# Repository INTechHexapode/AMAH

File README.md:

# AMAH : Automatic Markov-chain Actuated Hexapod
A hexapod robot that learns to walk by trial and errors, using Markov chain.

Please remark that I didn't design or build the robot itself (that was done by [Vincent Studer](https://fr.linkedin.com/in/vincent-studer-8179a864)).
My job was to program the leg control and the learning.

A few videos :
* [AMAH learns to stay upright](https://www.youtube.com/watch?v=HAIdLsz8gmg&feature=player_embedded)
* [Its first, painful walk](https://www.youtube.com/watch?v=2Z7JvmVVERA)
* [A presentation video, in french](https://www.youtube.com/watch?v=ZjIlJP-vDPI)
* [The dance of AMAH](https://www.facebook.com/190110074395003/videos/675518149187524/)

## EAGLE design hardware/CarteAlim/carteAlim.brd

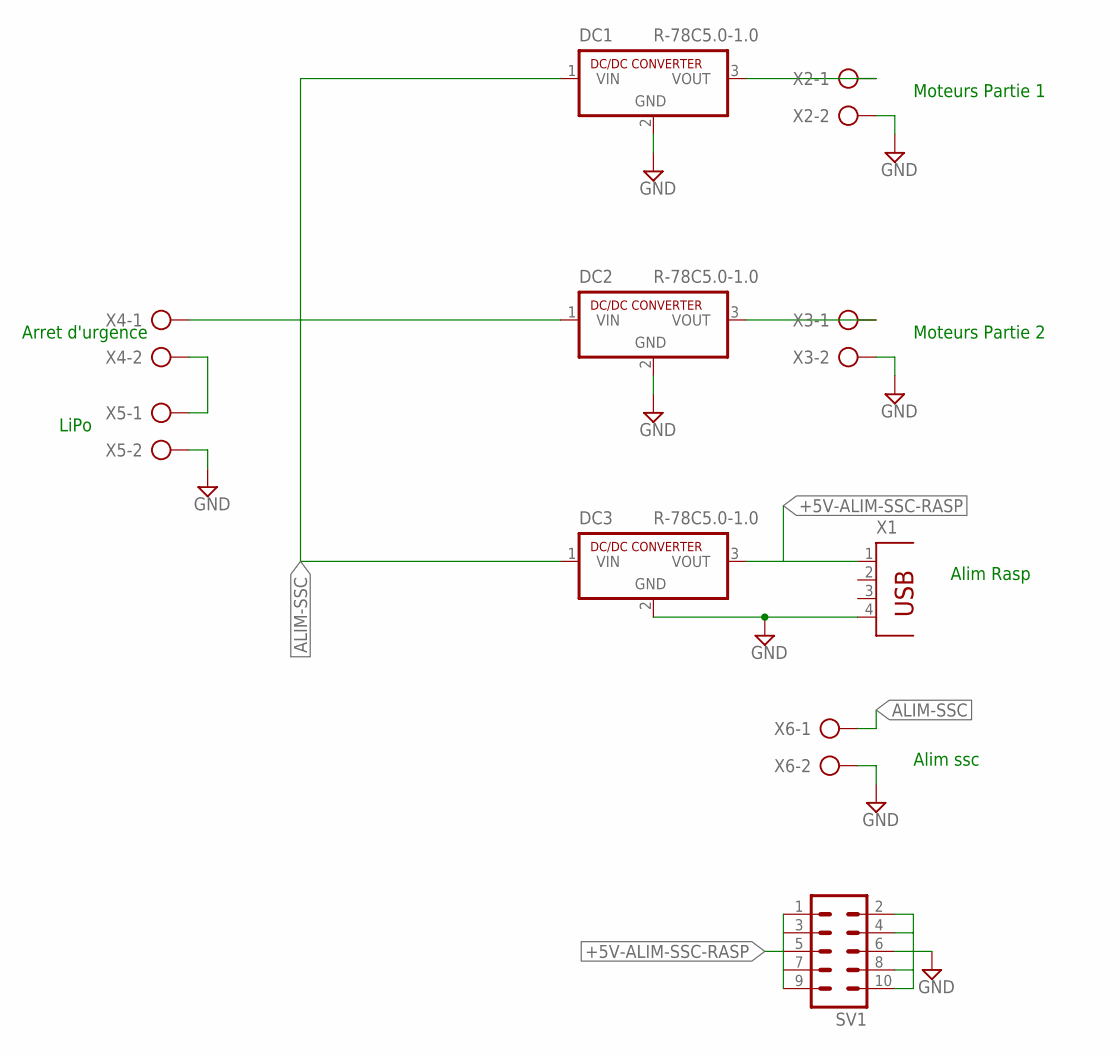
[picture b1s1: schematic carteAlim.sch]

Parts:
DC1, DC2, DC3: R-78C5.0-1.0; SIP3
SV1: MA05-2
X1: PN87520
X2, X3, X4, X5, X6: AK300/2

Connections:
+5V-ALIM-SSC-RASP: DC3.3 (VOUT), SV1.1, SV1.9, X1.1
ALIM-SSC: DC1.1 (VIN), DC2.1 (VIN), DC3.1 (VIN), X4.1, X6.1
GND: DC1.2 (GND), DC2.2 (GND), DC3.2 (GND), SV1.2, SV1.4, SV1.6, SV1.8, SV1.10, X1.4, X2.2, X3.2, X5.2, X6.2
unnamed: X4.2, X5.1
unnamed: DC1.3 (VOUT), X2.1
unnamed: DC2.3 (VOUT), X3.1

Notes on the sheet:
LiPo
Arret d'urgence
Moteurs Partie 1
Moteurs Partie 2
Alim Rasp
Alim ssc

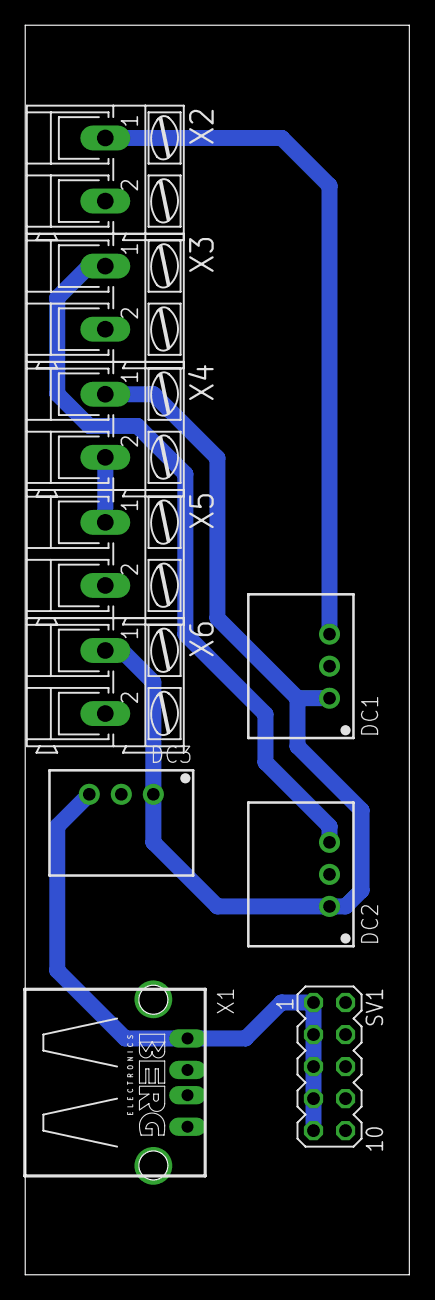
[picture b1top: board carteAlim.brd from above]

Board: 2 copper layers, 30.5 x 99.1 mm, 10 parts (0 on the bottom side), 6 nets.

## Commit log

2013-09-04 Mise en place de la structure du git
2013-09-04 Mise en place de la structure du git 2.0
2013-09-04 Ajout du script python
2013-09-06 Ajout de la classe serial
2013-09-06 Ajout des classes Hexapode, Servo et Leg
2013-09-06 Ajout de la compilatio nen C++11
2013-09-06 Test dans le main
2013-09-06 premiers tests, problème d'indexation des pattes dans Hexapod
2013-09-06 gitignore + modification de droits
2013-09-12 Ajout réseau de neuronne
2013-09-12 script python
2013-09-25 Ajout des 6 positions de pattes
2013-09-26 En mieux avec des enums
2014-02-10 Création du projet java
2014-02-10 Création des classes etat, hexapode, patte et moteur. Récupération du serialmanager d'intech.
2014-02-10 Complétion
2014-02-10 Une classe Markov aussi qui contiendra la chaîne
2014-02-11 EtatMoteur, EtatPatte, EtatHexa
2014-02-11 Oubli de commentaire
2014-02-12 Quelques TODO en plus
2014-02-17 Markov sérialisable
2014-02-17 Génération d'états aléatoires
2014-02-17 Quelques détails corrigés
2014-03-11 Ajout des classes pour gérer les enchaînements de tests
2014-03-11 Hexapode utilisé par le Test directement
2014-03-12 Rangement des classes de test dans un package à part
2014-03-15 Ping corrigé, lib en chemin relatif, protocole SSC-32
2014-03-16 Desasservissement, lever patte, baisser patte
2014-03-16 sauvegarde et chargement markov dans test, init() et terminate()
2014-03-16 Ajout init() et terminate() dans testEngine
2014-03-16 Lib série pour hexapode
2014-03-16 Encore serial
2014-03-16 Méthode change_moteur
2014-03-16 goto_etat de hexapode public
2014-03-16 Ajout de la méthode pour la maj matric
2014-03-16 Remplissage des fonctions de StandStill
2014-03-16 Getter et setter etat actuel sur hexapode
2014-03-16 Complétion de lever et baisser patte
2014-03-16 Correction du temps de pause et ajout de onBreak()
2014-03-16 Patte et EtatPatte
2014-03-16 init() dans le constructeur du testEngine
2014-03-16 On est presque prêt pour les tests
2014-03-16 Suppression de warnings
2014-03-17 Test réalisable, sérialisation à debugger
2014-03-17 .gitignore pour les sauvegardes de matrices
2014-03-17 Des commentaires
2014-03-18 classpath et project dans le gitignore
2014-03-18 Tuto à partir de zéro pour apprendre à installer la librxtx!!
2014-03-18 Premières sauvegardes de matrice
2014-03-18 Sauvegarde complète (avec logs/ aussi) ou partielle (sans logs/)
2014-03-18 ValidTest, sérialisation, accélération de l'apprentissage (on ne remonte que si on en a besoin)
2014-03-19 Debut de code pour l'affichage (n'est pas encore intégré)
2014-03-19 4 états pattes, debug test, log
2014-03-19 Markov avec 4 états
2014-03-19 série > /dev/null
2014-03-19 Surcharge next() avec la matrice pour tenir debout
2014-03-19 calculs à debugger
2014-03-24 Toujours pas possible de se servir de l'interface graphique, mais ça avance un minimum
2014-03-26 Ajout de la classe DataSaver qui encapsule des fonctions de sauvegarde et chargement des données.
2014-03-27 Sauvegarde de chaque étape du test pour pouvoir le rejouer plus tard. Non testé loul
2014-04-24 Et un gros commit qui tache avec trop de choses pour que je me souvienne de tout :
    - Grosse modif de markov pour avoir une matrice à deux dimension
    (standstilltest ne fonctionnera plus)
    - Début du test de coordination des pattes
2014-04-24 Ajout de la classe SocketClient, permettant de communiquer avec l'appli Android
2014-04-25 Conversion coordonnées (x,y) -> angles
2014-04-25 DataSaver avec suppression de fichiers
2014-04-25 Symétrie circulaire
2014-04-25 EtatPatte avec les nouveaux états
2014-04-25 Hexapode fait l'action contenue dans un String
2014-04-25 Debug patte et Markov
2014-04-25 Ajout du test d'apprentissage pour la coordination des pattes
2014-04-25 Rename des data
2014-04-25 EtatPatte peut aller à toutes les positions... mais faut encore debugger
2014-04-25 Ajout de l'override de toString
2014-04-25 Modification de next() pour renvoyer une position d'équilibre
2014-04-25 Ajout de l'etat_actuel comme attribut de Test. Rajout du nouveau test pour la coordination des pattes.
2014-04-25 Ménage de printemps, simplification, exception
2014-04-26 Ajout du test de simulation MAJ des données markov_equilibre Divers debugs, test de simulation toujours à debug.
2014-04-26 Suite du debug. TODO : Fix le save_test (classenon serializable) Check le getNum et la taille de la matrice
2014-04-26 Correction formule
2014-04-26 Test
2014-04-26 Ça marche super, rotation y compris
2014-04-26 MAJ EtatPatte => String
2014-04-26 Moteurs groupés
2014-04-26 Simulation fonctionne, rework EtatPatte=>String terminé
2014-04-26 Il en manquait un, loul
2014-04-26 simulation qui marche, valeurs à valider
2014-04-26 validation de test simulation
2014-04-26 Chargement matrice validation
2014-04-26 Gestion du temps
2014-04-26 Lanceur avec plusieurs méthodes disponibles
2014-04-26 Debug markov
2014-04-26 Méthodes haut niveau pour hexapode (avancer, va_au_point)
2014-04-26 goto_etat ne renvoie plus d'exception mais les traite lui-même
2014-04-26 Nouvelle marche à tester
2014-04-26 Méthode recaler, poser_fresque, symétrie rouge/jaune
2014-04-26 TODO list
2014-04-26 Correction angles min et max
2014-04-26 Quelques petites optimisations de code
2014-04-26 Vec2, suit_chemin
2014-04-26 Trajectoire horaire ou anti-horaire
2014-04-27 recaler réécrite
2014-04-27 De plus grandes enjambées
2014-04-27 Fin du match
2014-04-27 Utilisation du capteur
2014-04-27 Contournement de l'ennemi
2014-04-27 Gestion des bordures du terrain
2014-04-27 Ecart à la bordure
2014-04-27 Petit oubli
2014-04-27 Distance de détection
2014-04-27 Marche en ignorant certaines pattes
2014-04-27 Réorganisation du fichier Hexapode: les méthodes haut niveau sont en haut, les bas niveau en bas
2014-04-27 Debug + constantes
2014-04-27 Debug
2014-04-27 Debug au_au_point
2014-04-27 Pareil, mais sans les print
2014-04-27 Profils de marche (enjamber, aller loin, ...)
2014-04-27 J'ai essayé un mouvement triphasé, mais ça ne marche pas...
2014-04-27 Le lanceur aussi
2014-04-27 Baudrate à 38400
2014-04-27 On ne doit normalement pas spécifier de temps pour un moteur désasservi (cf datasheet)
2014-04-27 Commentaires, visibilité
2014-04-27 Package d'enumérations
2014-04-28 Ajout de l'appli android sur le dépot, désolé...
2014-04-28 Carte Alim
2014-04-28 Capteur
2014-04-28 Test coordination triphasée
2014-04-28 Lanceur trop cool qui met automatiquement en simulation si y'a pas de série
2014-04-28 Coordination triphasée en partie débuggée
2014-04-28 Debug. Normalement, tout marche bien!
2014-04-29 Changer direction plus propre dans les mouvements des pattes.
2014-04-29 On ignore les markov qui sont dans logs/
2014-04-29 Structure des tests légèrement changée
2014-04-29 Des enums tout mignon pour coder proprement
2014-04-29 Pas d'attente au début en simulation
2014-04-29 Debug hexapode
2014-04-29 On lève plus les pattes.
2014-04-29 Enum profil
2014-04-29 On pourra utiliser les chaînes de Markov dans les match. Je sais pas si on le fera, mais en tout cas on pourra.
2014-04-29 Séparation des déplacements bas niveau (Deplacement) et haut niveau (Hexapode).
2014-04-29 Markov biphasé et triphasé. Bonne précision, mais peut faire mieux.
2014-04-29 Debug, chargement des chaînes de Markov dans déplacement
2014-04-29 gestion des capteurs
2014-04-30 Il faut modifier la marche aussi si on veut modifier le mode.
2014-04-30 Injection de dépendances, compression de matrice
2014-04-30 TestOrientation (pas encore fini)
2014-05-05 Amélioration de l'affichage
2014-05-05 Ajout du "calcul" de bruit plus d'une lib pour l'affichage
2014-05-05 MAJ de l'appli android
2014-05-05 Suppression de warning
2014-05-05 Testez votre code qui disait... J'ai pas push la bonne version de mon code de l'appli Android, mais maintenant c'est bon
2014-05-13 Modification facile de l'angle
2014-05-15 Markov2Coups, décision, ...
2014-05-15 Script fresques
2014-05-15 Symétrie, fin du match plus propre
2014-05-16 Une meilleure gestion des différentes marches (biphasé, etc.)
2014-05-27 Voilà le patch de la carte d'alim!
2014-05-27 IL EST LAAAAAAAA (pour raspberry)
2014-05-27 Arrêt au bout de 85s pour avoir le temps de s'arrêter
2014-05-27 Va au point relatif
2014-05-27 lanceur à faire...
2014-05-28 lanceur
2014-05-28 capteurs
2014-05-28 Corrections première marche sur table
2014-05-28 Angles à revoir
2014-05-28 Moins de latence dans la mesure
2014-05-28 Coupe
2014-05-28 millis ne doit pas être négatif
2014-05-28 tests
2014-05-29 Prêt pour l'homologation
2014-05-29 Evitement
2014-05-29 abwabwa
2014-05-29 lanceur coupe
2014-05-29 dance
2014-05-31 la coupe c'est fini
2014-06-09 Debug pour la soutenance
2014-06-09 Matrice biphasée pour cent millions d'itérations
2014-06-09 lanceur biphasé et triphasé
2014-06-21 dernière version
2017-02-26 Create LICENSE
2017-10-23 Add a video and some pictures
